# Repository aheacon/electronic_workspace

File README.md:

# electronic_workspace
This is my electronic workspace

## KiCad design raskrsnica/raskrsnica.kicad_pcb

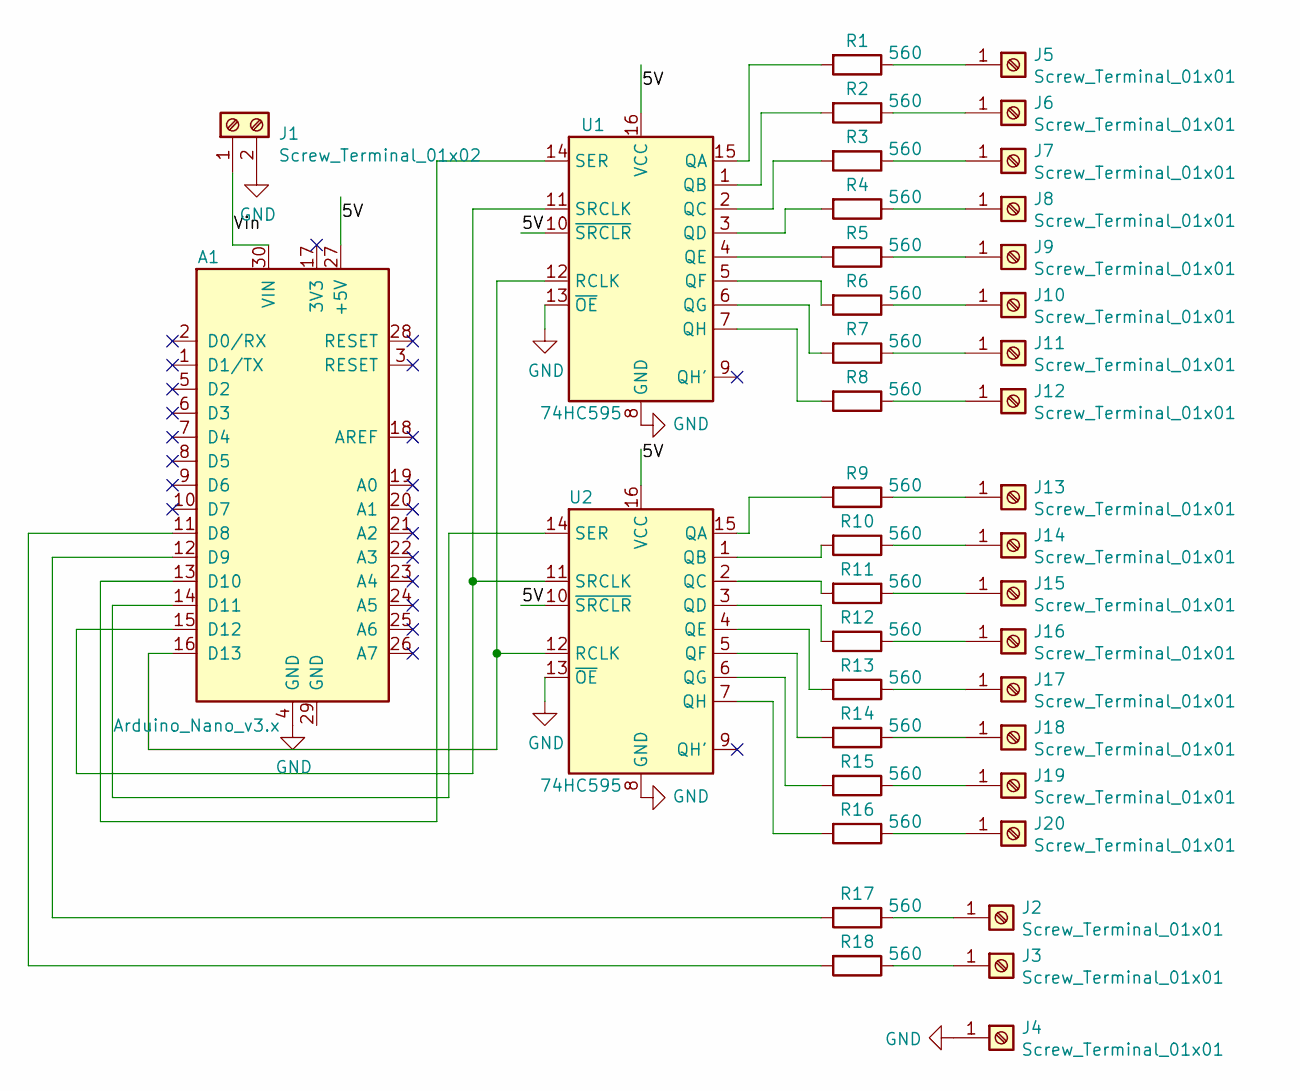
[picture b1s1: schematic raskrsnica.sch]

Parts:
A1: Arduino_Nano_v3.x; Arduino_Nano
J1: Screw_Terminal_01x02; R_Axial_DIN0207_L6.3mm_D2.5mm_P7.62mm_Horizontal
J2, J3, J4, J5, J6, J7, J8, J9, J10, J11, J12, J13, J14, J15, J16, J17, J18, J19, J20: Screw_Terminal_01x01; TerminalBlock_MetzConnect_360271_1x01_Horizontal_ScrewM3.0_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
R1, R2, R3, R4, R5, R6, R7, R8, R9, R10, R11, R12, R13, R14, R15, R16, R17, R18: 560; R_Axial_DIN0207_L6.3mm_D2.5mm_P7.62mm_Horizontal
U1, U2: 74HC595; DIP-16_W7.62mm

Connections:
/5V: A1.27 (+5V), U1.10 (~SRCLR), U1.16 (VCC), U2.10 (~SRCLR), U2.16 (VCC)
/Vin: A1.30 (VIN), J1.1
GND: A1.4 (GND), J1.2, J4.1, U1.8 (GND), U1.13 (~OE), U2.8 (GND), U2.13 (~OE)
unnamed: A1.11 (D8), R18.2
unnamed: A1.12 (D9), R17.2
unnamed: A1.13 (D10), U1.14 (SER)
unnamed: A1.14 (D11), U2.14 (SER)
unnamed: A1.15 (D12), U1.11 (SRCLK), U2.11 (SRCLK)
unnamed: A1.16 (D13), U1.12 (RCLK), U2.12 (RCLK)
unnamed: J2.1, R17.1
unnamed: J3.1, R18.1
unnamed: J5.1, R1.1
unnamed: J6.1, R2.1
unnamed: J7.1, R3.1
unnamed: J8.1, R4.1
unnamed: J9.1, R5.1
unnamed: J10.1, R6.1
unnamed: J11.1, R7.1
unnamed: J12.1, R8.1
unnamed: J13.1, R9.1
unnamed: J14.1, R10.1
unnamed: J15.1, R11.1
unnamed: J16.1, R12.1
unnamed: J17.1, R13.1
unnamed: J18.1, R14.1
unnamed: J19.1, R15.1
unnamed: J20.1, R16.1
unnamed: R1.2, U1.15 (QA)
unnamed: R2.2, U1.1 (QB)
unnamed: R3.2, U1.2 (QC)
unnamed: R4.2, U1.3 (QD)
unnamed: R5.2, U1.4 (QE)
unnamed: R6.2, U1.5 (QF)
unnamed: R7.2, U1.6 (QG)
unnamed: R8.2, U1.7 (QH)
unnamed: R9.2, U2.15 (QA)
unnamed: R10.2, U2.1 (QB)
unnamed: R11.2, U2.2 (QC)
unnamed: R12.2, U2.3 (QD)
unnamed: R13.2, U2.4 (QE)
unnamed: R14.2, U2.5 (QF)
unnamed: R15.2, U2.6 (QG)
unnamed: R16.2, U2.7 (QH)

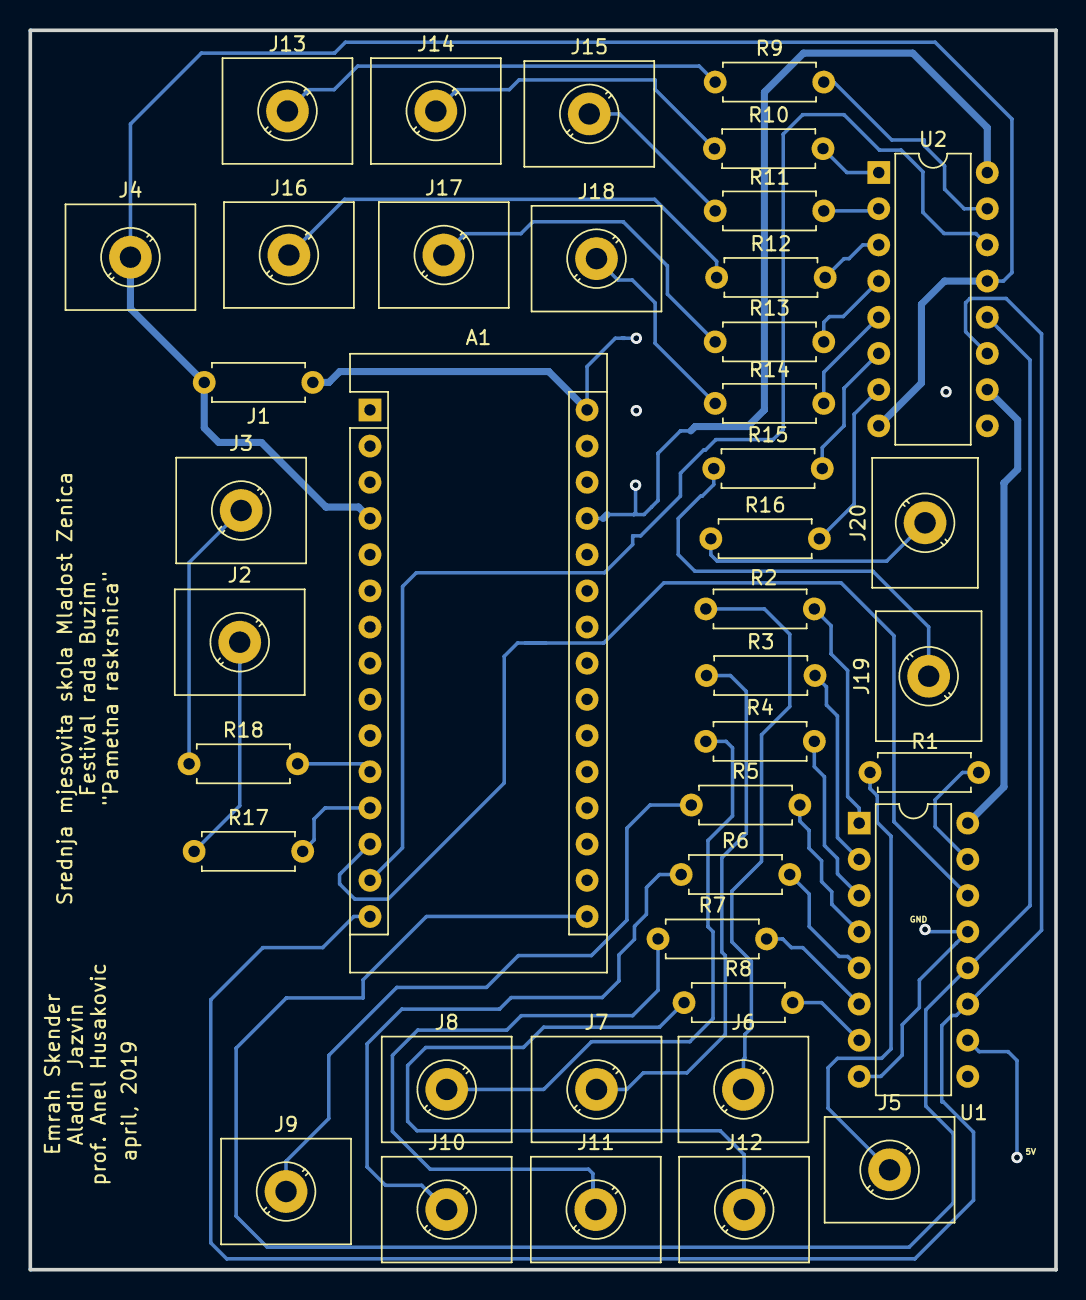
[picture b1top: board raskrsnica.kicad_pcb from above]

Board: 2 copper layers, 72.0 x 87.0 mm, 41 parts (0 on the bottom side), 43 nets.

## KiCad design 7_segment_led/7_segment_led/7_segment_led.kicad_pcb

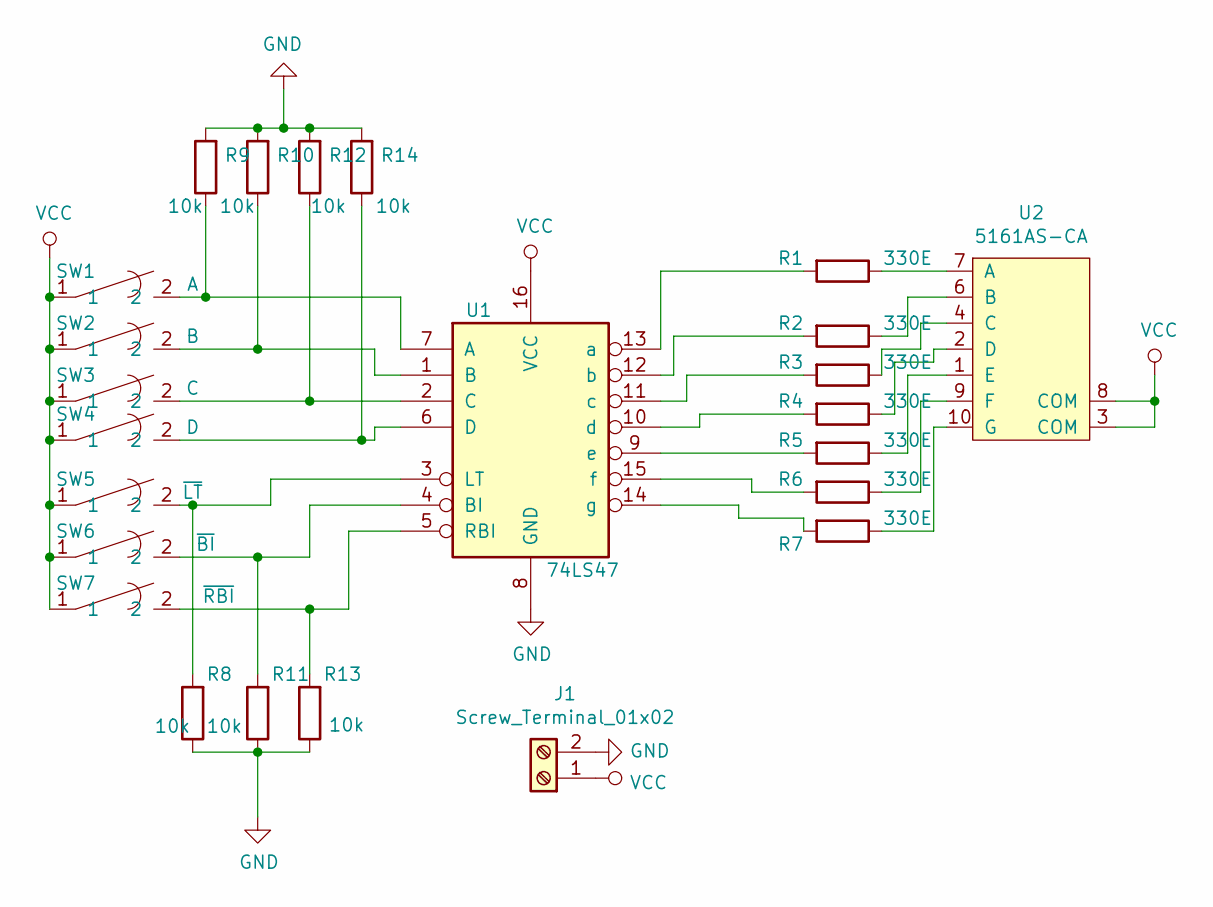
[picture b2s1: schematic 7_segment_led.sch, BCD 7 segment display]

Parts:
J1: Screw_Terminal_01x02; TerminalBlock_bornier-2_P5.08mm
R1, R2, R3, R4, R5, R6, R7: 330E; R_Axial_DIN0207_L6.3mm_D2.5mm_P7.62mm_Horizontal
R8, R9, R10, R11, R12, R13, R14: 10k; R_Axial_DIN0207_L6.3mm_D2.5mm_P7.62mm_Horizontal
SW1: A; SW_PUSH_6mm
SW2: B; SW_PUSH_6mm
SW3: C; SW_PUSH_6mm
SW4: D; SW_PUSH_6mm
SW5: ~LT; SW_PUSH_6mm
SW6: ~BI; SW_PUSH_6mm
SW7: ~RBI; SW_PUSH_6mm
U1: 74LS47; DIP-16_W7.62mm
U2: 5161AS-CA; 7SegmentLED_LTS6760_LTS6780

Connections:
GND: J1.2, R8.1, R9.2, R10.2, R11.1, R12.2, R13.1, R14.2, U1.8 (GND)
unnamed: R1.1, U2.7 (A)
unnamed: R1.2, U1.13 (a)
unnamed: R2.1, U2.6 (B)
unnamed: R2.2, U1.12 (b)
unnamed: R3.1, U2.4 (C)
unnamed: R3.2, U1.11 (c)
unnamed: R4.1, U2.2 (D)
unnamed: R4.2, U1.10 (d)
unnamed: R5.1, U2.1 (E)
unnamed: R5.2, U1.9 (e)
unnamed: R6.1, U2.9 (F)
unnamed: R6.2, U1.15 (f)
unnamed: R7.1, U2.10 (G)
unnamed: R7.2, U1.14 (g)
unnamed: R8.2, SW5.2, U1.3 (LT)
unnamed: R9.1, SW1.2, U1.7 (A)
unnamed: R10.1, SW2.2, U1.1 (B)
unnamed: R11.2, SW6.2, U1.4 (BI)
unnamed: R12.1, SW3.2, U1.2 (C)
unnamed: R13.2, SW7.2, U1.5 (RBI)
unnamed: R14.1, SW4.2, U1.6 (D)
VCC: J1.1, SW1.1, SW2.1, SW3.1, SW4.1, SW5.1, SW6.1, SW7.1, U1.16 (VCC), U2.3 (COM), U2.8 (COM)

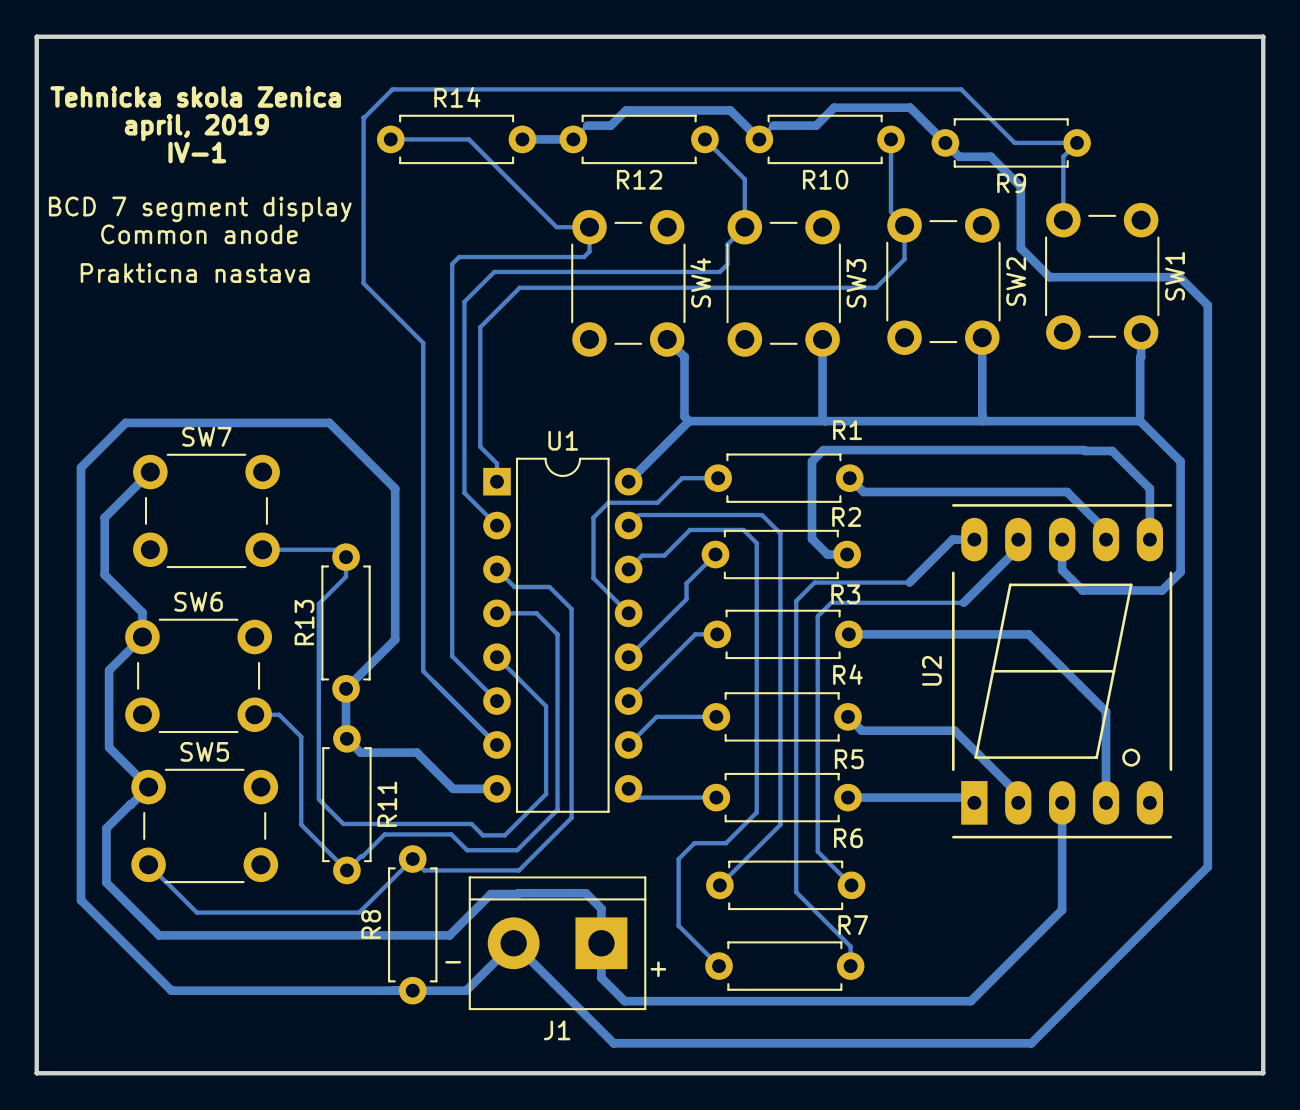
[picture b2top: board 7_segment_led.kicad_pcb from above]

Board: 2 copper layers, 71.0 x 60.0 mm, 24 parts (0 on the bottom side), 23 nets.

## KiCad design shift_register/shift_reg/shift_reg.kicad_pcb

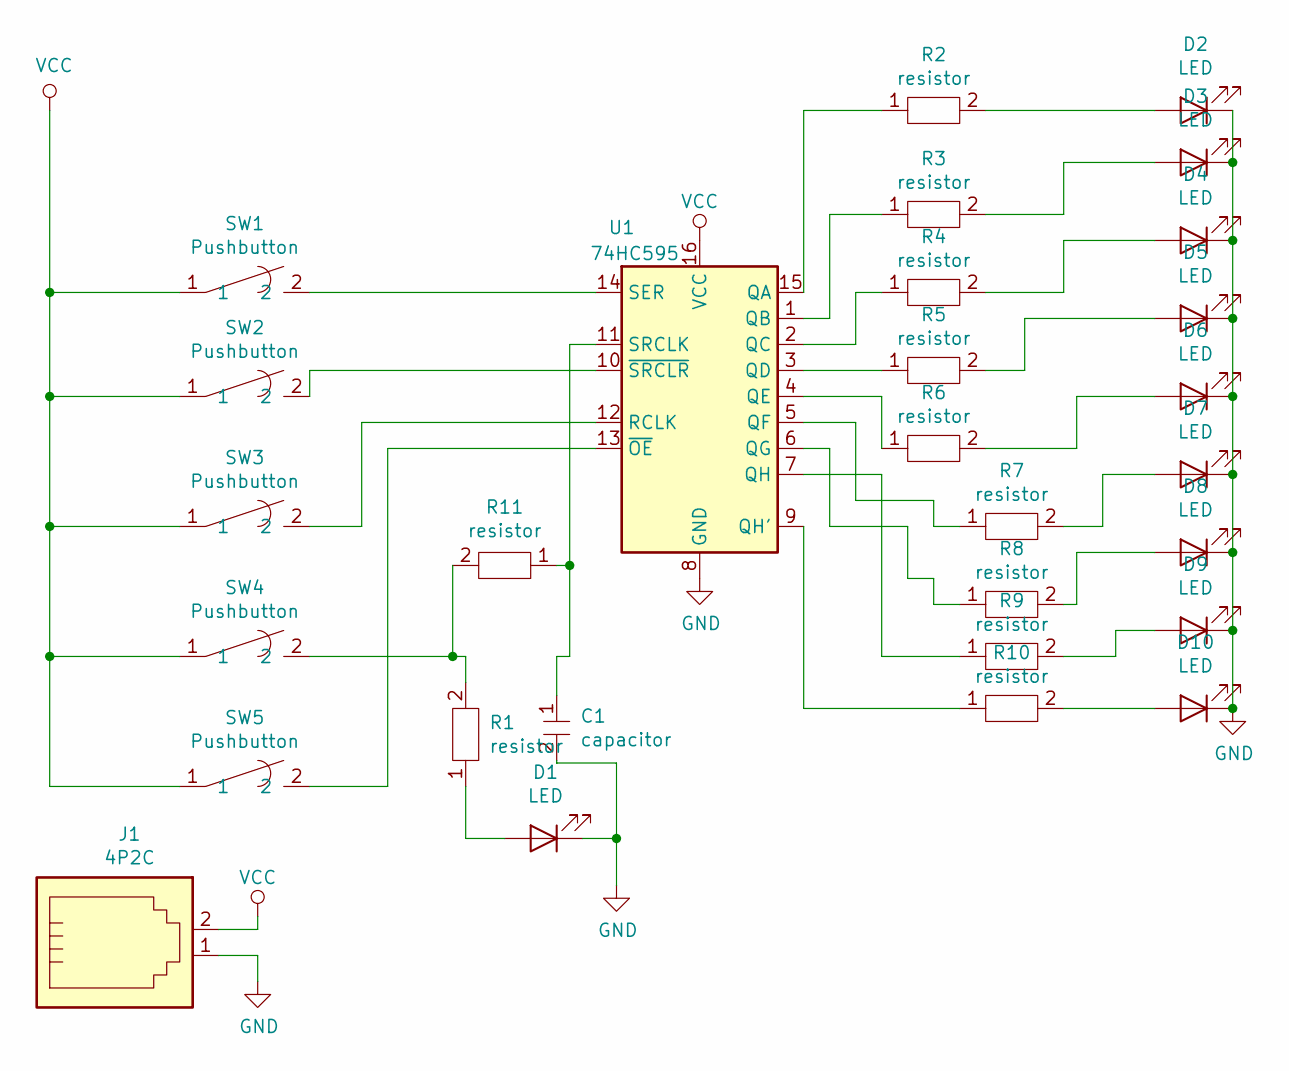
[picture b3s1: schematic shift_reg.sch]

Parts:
C1: capacitor; LED_D5.0mm_Clear
D1, D2, D3, D4, D5, D6, D7, D8, D9, D10: LED; LED_D5.0mm_Clear
J1: 4P2C; TerminalBlock_bornier-2_P5.08mm
R1, R2, R3, R4, R5, R6, R7, R8, R9, R10, R11: resistor; R_Axial_DIN0207_L6.3mm_D2.5mm_P7.62mm_Horizontal
SW1, SW2, SW3, SW4, SW5: Pushbutton; SW_PUSH_6mm
U1: 74HC595; DIP-16_W7.62mm_LongPads

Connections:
GND: C1.2, D1.1 (K), D2.1 (K), D3.1 (K), D4.1 (K), D5.1 (K), D6.1 (K), D7.1 (K), D8.1 (K), D9.1 (K), D10.1 (K), J1.1, U1.8 (GND)
unnamed: C1.1, R11.1, U1.11 (SRCLK)
unnamed: D1.2 (A), R1.1
unnamed: D2.2 (A), R2.2
unnamed: D3.2 (A), R3.2
unnamed: D4.2 (A), R4.2
unnamed: D5.2 (A), R5.2
unnamed: D6.2 (A), R6.2
unnamed: D7.2 (A), R7.2
unnamed: D8.2 (A), R8.2
unnamed: D9.2 (A), R9.2
unnamed: D10.2 (A), R10.2
unnamed: R1.2, R11.2, SW4.2
unnamed: R2.1, U1.15 (QA)
unnamed: R3.1, U1.1 (QB)
unnamed: R4.1, U1.2 (QC)
unnamed: R5.1, U1.3 (QD)
unnamed: R6.1, U1.4 (QE)
unnamed: R7.1, U1.5 (QF)
unnamed: R8.1, U1.6 (QG)
unnamed: R9.1, U1.7 (QH)
unnamed: R10.1, U1.9 (QH')
unnamed: SW1.2, U1.14 (SER)
unnamed: SW2.2, U1.10 (~SRCLR)
unnamed: SW3.2, U1.12 (RCLK)
unnamed: SW5.2, U1.13 (~OE)
VCC: J1.2, SW1.1, SW2.1, SW3.1, SW4.1, SW5.1, U1.16 (VCC)

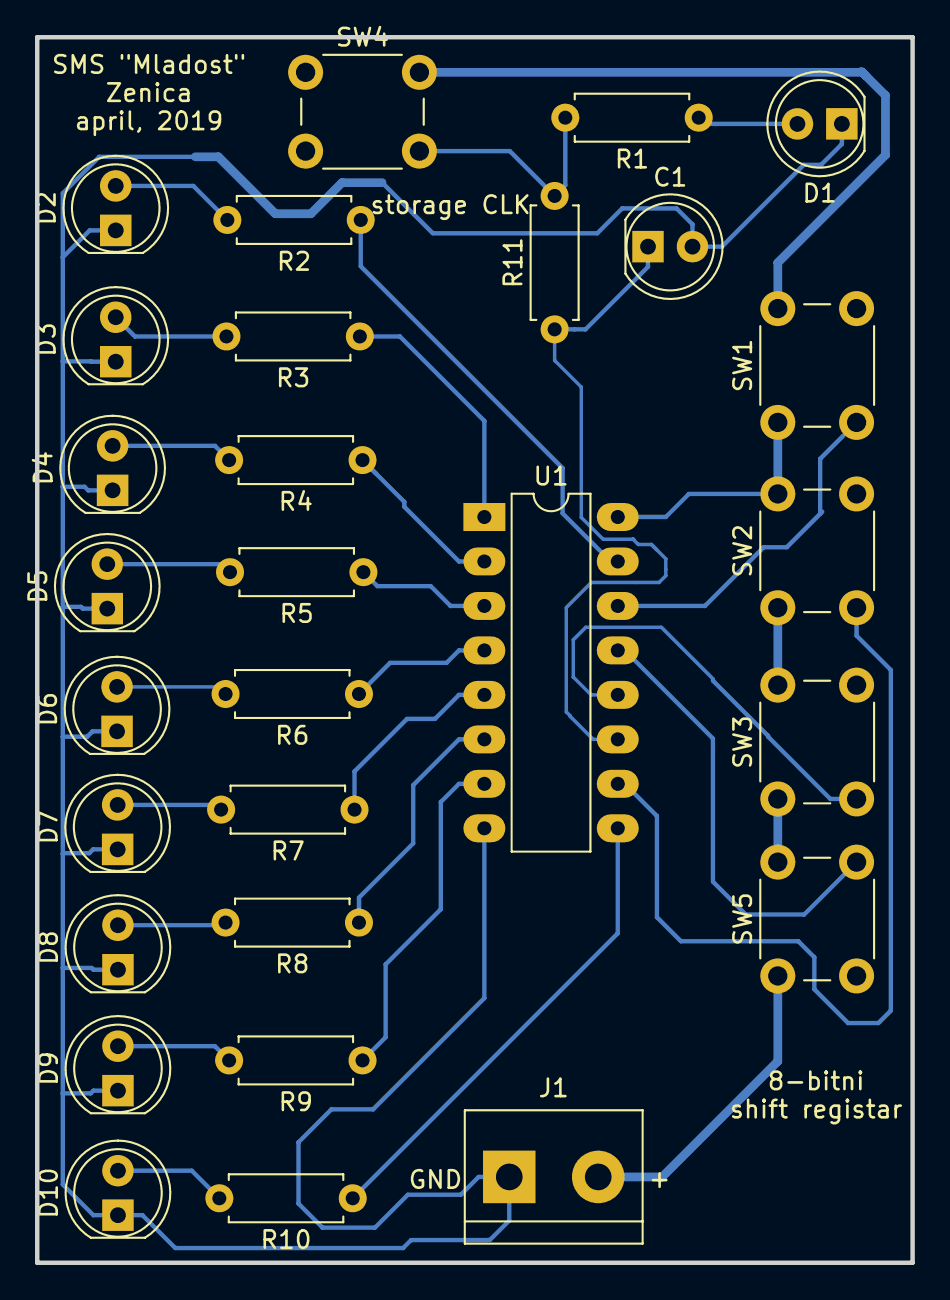
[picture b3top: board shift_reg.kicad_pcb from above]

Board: 2 copper layers, 50.0 x 70.0 mm, 29 parts (0 on the bottom side), 27 nets.

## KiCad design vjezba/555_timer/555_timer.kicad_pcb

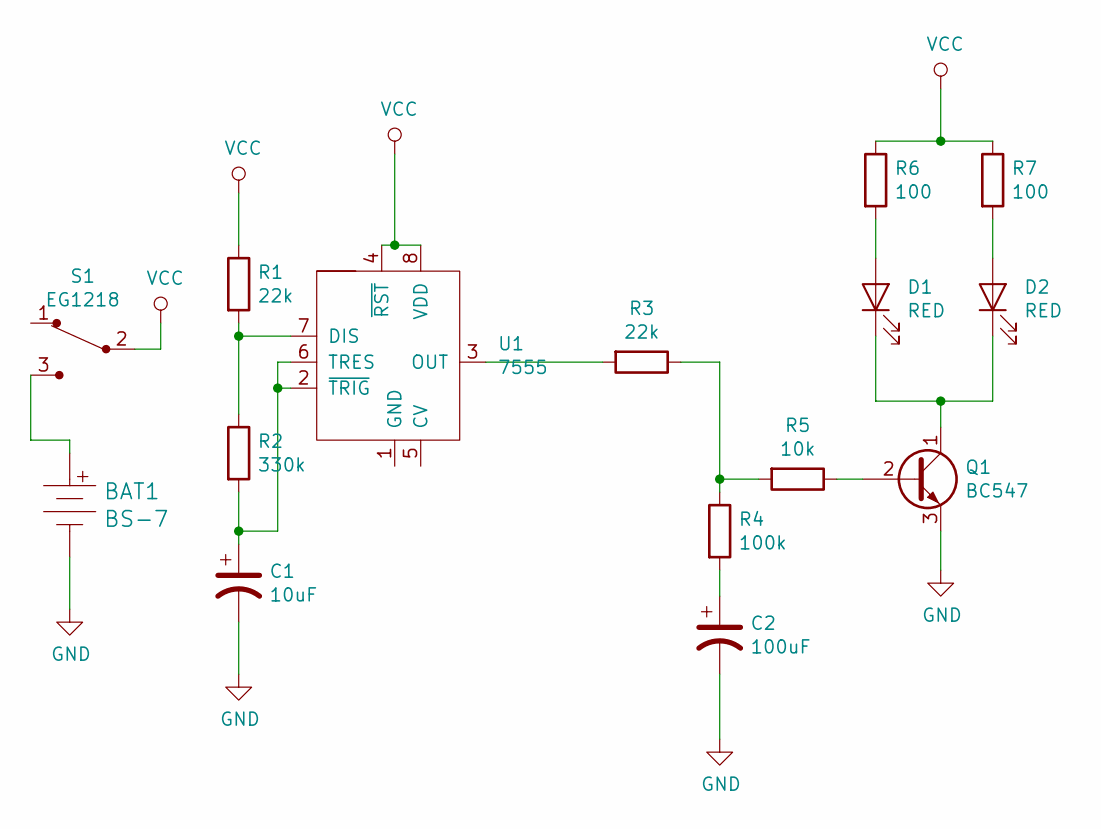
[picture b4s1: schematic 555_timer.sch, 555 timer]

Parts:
BAT1: BS-7; Battery_Holder_Coin_2032_BS-7; MPN BS-7; Digi-Key_PN BS-7-ND
C1: 10uF; CP_Radial_D5.0mm_P2.00mm
C2: 100uF; CP_Radial_D6.3mm_P2.50mm
D1, D2: RED; LED_D5.0mm_Clear
Q1: BC547; TO-92_Inline
R1, R3: 22k; R_Axial_DIN0207_L6.3mm_D2.5mm_P7.62mm_Horizontal
R2: 330k; R_Axial_DIN0207_L6.3mm_D2.5mm_P7.62mm_Horizontal
R4: 100k; R_Axial_DIN0207_L6.3mm_D2.5mm_P7.62mm_Horizontal
R5: 10k; R_Axial_DIN0207_L6.3mm_D2.5mm_P7.62mm_Horizontal
R6, R7: 100; R_Axial_DIN0207_L6.3mm_D2.5mm_P7.62mm_Horizontal
S1: EG1218; Switch_Slide_11.6x4mm_EG1218; MPN EG1218; Digi-Key_PN EG1903-ND
U1: 7555; 7555-PDIP

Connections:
GND: BAT1.Neg, C1.2, C2.2, Q1.3 (E)
unnamed: BAT1.Pos, S1.3
unnamed: C1.1, R2.2, U1.2 (~TRIG), U1.6 (TRES)
unnamed: C2.1, R4.2
unnamed: D1.1 (K), D2.1 (K), Q1.1 (C)
unnamed: D1.2 (A), R6.2
unnamed: D2.2 (A), R7.2
unnamed: Q1.2 (B), R5.1
unnamed: R1.2, R2.1, U1.7 (DIS)
unnamed: R3.1, R4.1, R5.2
unnamed: R3.2, U1.3 (OUT)
VCC: R1.1, R6.1, R7.1, S1.2, U1.4 (~RST), U1.8 (VDD)

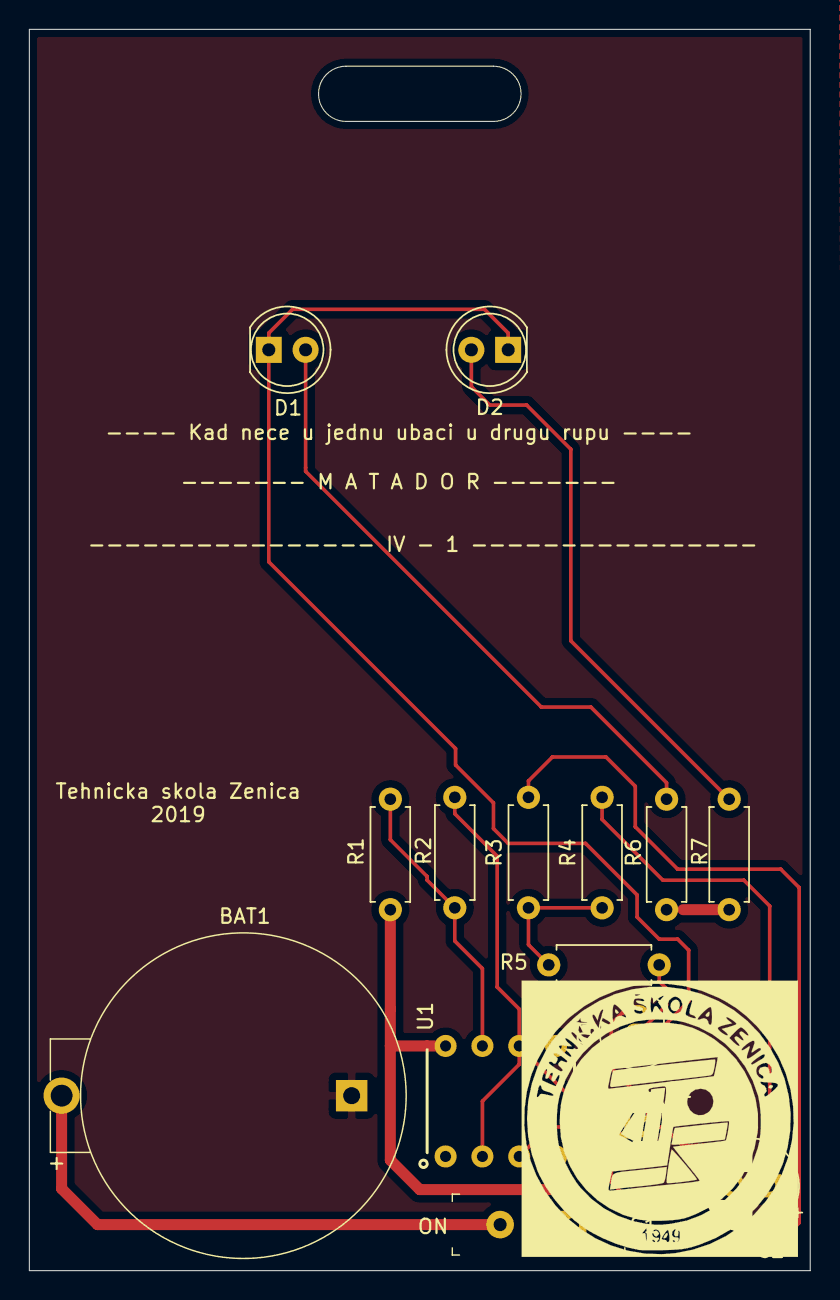
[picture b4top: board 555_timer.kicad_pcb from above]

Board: 2 copper layers, 53.8 x 85.6 mm, 15 parts (0 on the bottom side), 12 nets.

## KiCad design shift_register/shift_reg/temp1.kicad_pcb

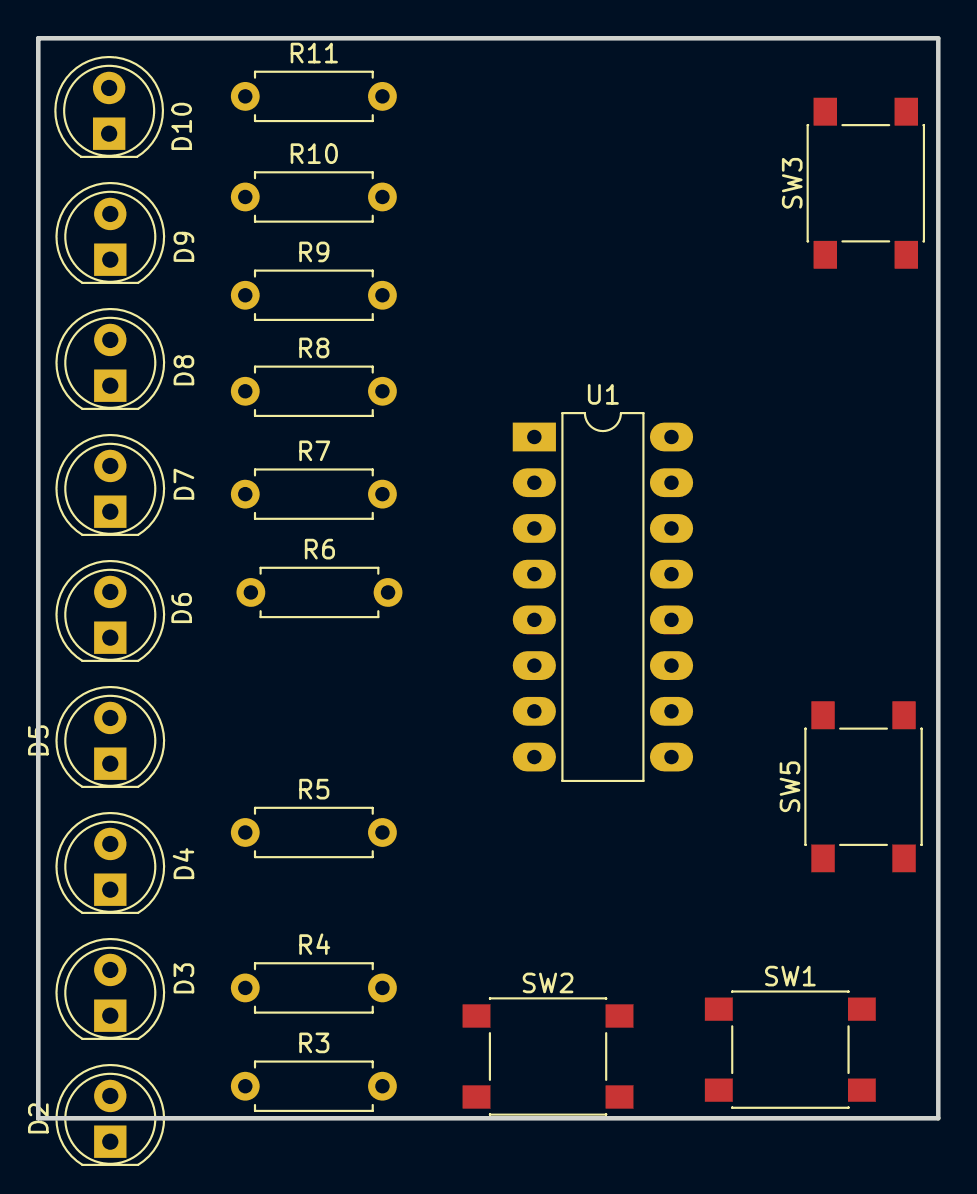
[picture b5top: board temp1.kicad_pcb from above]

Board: 2 copper layers, 50.0 x 60.0 mm, 23 parts (0 on the bottom side), 22 nets, no tracks yet.

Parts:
D2, D3, D4, D5, D6, D7, D8, D9, D10: LED; LED_D5.0mm_Clear
R3, R4, R5, R6, R7, R8, R9, R10, R11: R; R_Axial_DIN0207_L6.3mm_D2.5mm_P7.62mm_Horizontal
SW1: RCLK; SW_Push_1P1T_NO_6x6mm_H9.5mm
SW2: ~OE; SW_Push_1P1T_NO_6x6mm_H9.5mm
SW3: SER; SW_Push_1P1T_NO_6x6mm_H9.5mm
SW5: ~CLR; SW_Push_1P1T_NO_6x6mm_H9.5mm
U1: 74HC595; DIP-16_W7.62mm_LongPads

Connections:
GND: D2.1, D3.1, D4.1, D5.1, D6.1, D7.1, D8.1, D9.1, D10.1, U1.8
unnamed: D2.2, R3.1
unnamed: D3.2, R4.1
unnamed: D4.2, R5.1
unnamed: D5.2, R6.1
unnamed: D6.2, R7.1
unnamed: D7.2, R8.1
unnamed: D8.2, R9.1
unnamed: D9.2, R10.1
unnamed: D10.2, R11.1
unnamed: R3.2, U1.15
unnamed: R4.2, U1.1
unnamed: R5.2, U1.2
unnamed: R6.2, U1.3
unnamed: R7.2, U1.4
unnamed: R8.2, U1.5
unnamed: R9.2, U1.6
unnamed: R10.2, U1.7
unnamed: R11.2, U1.9
unnamed: SW2.2, U1.13
unnamed: SW3.2, U1.14
VCC: SW2.1, SW3.1, SW5.1, U1.16

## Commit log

2019-04-13 Test commit
2019-04-18 Tutorials
2019-04-18 Shift register
2019-04-19 Gerbers pdfs for shift registers
2019-04-19 BCD 7 segment display Common Anode 5161AS
2019-04-20 Raskrsinca v1 with LEDs and 2 shift registers
2019-04-21 Raskrsnica sa konektorima -PCB not done
2019-04-21 Layot ver 1
2019-04-21 Layot ver 2
2019-04-21 Raskrsnica layout finished
2019-04-21 Add gerbers and pdfs
2019-04-22 Add schematic pdf
